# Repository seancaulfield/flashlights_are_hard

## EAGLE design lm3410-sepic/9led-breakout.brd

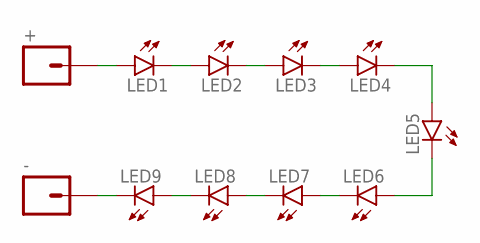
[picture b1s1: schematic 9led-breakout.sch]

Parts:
+: M01PTH-KIT; 1X01-KIT
-: M01NOSILK-KIT; 1X01NS-KIT
LED1, LED2, LED3, LED4, LED5, LED6, LED7, LED8, LED9: LED5MM

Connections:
unnamed: +.1, LED1.A
unnamed: LED1.K (C), LED2.A
unnamed: LED2.K (C), LED3.A
unnamed: LED3.K (C), LED4.A
unnamed: LED4.K (C), LED5.A
unnamed: LED5.K (C), LED6.A
unnamed: LED6.K (C), LED7.A
unnamed: LED7.K (C), LED8.A
unnamed: LED8.K (C), LED9.A
unnamed: -.1, LED9.K (C)

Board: 2 copper layers, 11 parts (0 on the bottom side), 10 nets, no tracks yet.

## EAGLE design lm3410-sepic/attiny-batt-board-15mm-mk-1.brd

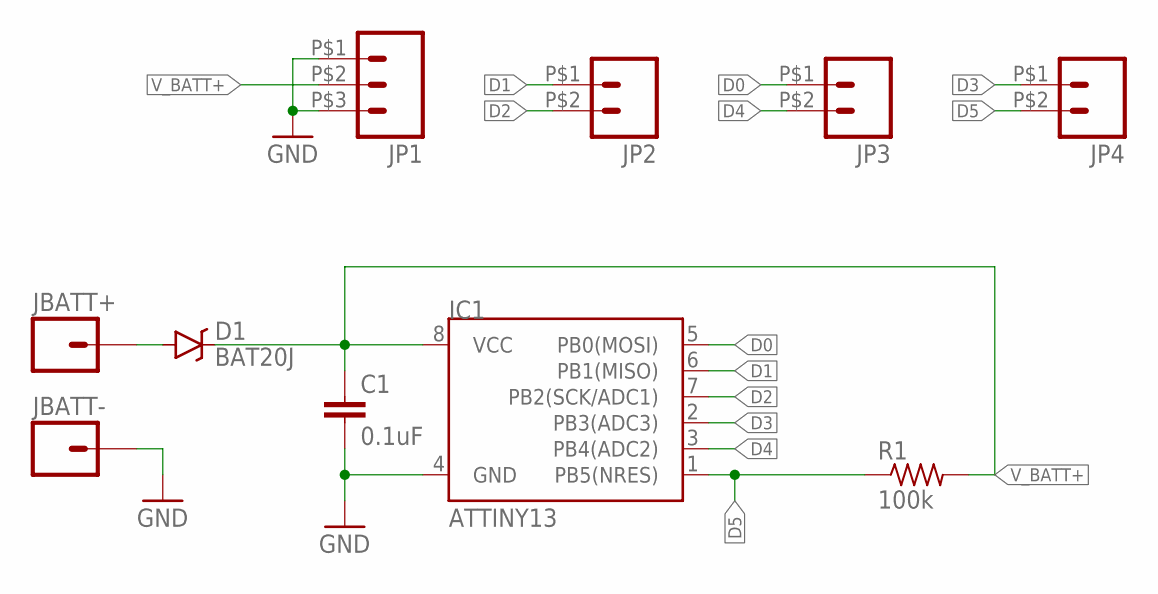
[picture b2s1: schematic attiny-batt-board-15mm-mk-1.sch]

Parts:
C1: 0.1uF; C0603
D1: BAT20J; SOD-323
IC1: ATTINY13; SO08
JBATT+: M01NOT-A-VIA-NOPE; 1X01_NOSILK_NOSTOP
JBATT-: M01NOT-A-VIA-NOPE; 1X01_NOSILK_NOSTOP
JP1: M03PTH-2MM; 1X03-2MM-PTH
JP2, JP3, JP4: M02PTH-2MM; 1X02-2MM-PTH
R1: 100k; R0603

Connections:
BATT_IN: D1.A, JBATT+.P$1
D0: IC1.5 (PB0(MOSI)), JP3.P$1 (1)
D1: IC1.6 (PB1(MISO)), JP2.P$1 (1)
D2: IC1.7 (PB2(SCK/ADC1)), JP2.P$2 (2)
D3: IC1.2 (PB3(ADC3)), JP4.P$1 (1)
D4: IC1.3 (PB4(ADC2)), JP3.P$2 (2)
D5: IC1.1 (PB5(NRES)), JP4.P$2 (2), R1.1
GND: C1.2, IC1.4 (GND), JBATT-.P$1, JP1.P$1 (1), JP1.P$3 (3)
V_BATT+: C1.1, D1.C, IC1.8 (VCC), JP1.P$2 (2), R1.2

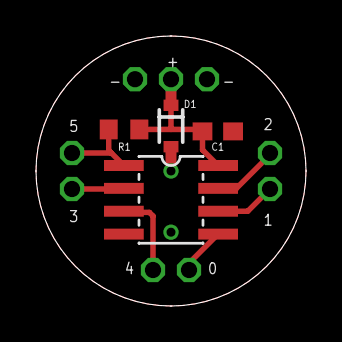
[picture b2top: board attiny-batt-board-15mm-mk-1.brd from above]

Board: 2 copper layers, 15.0 x 15.0 mm, 10 parts (0 on the bottom side), 9 nets.

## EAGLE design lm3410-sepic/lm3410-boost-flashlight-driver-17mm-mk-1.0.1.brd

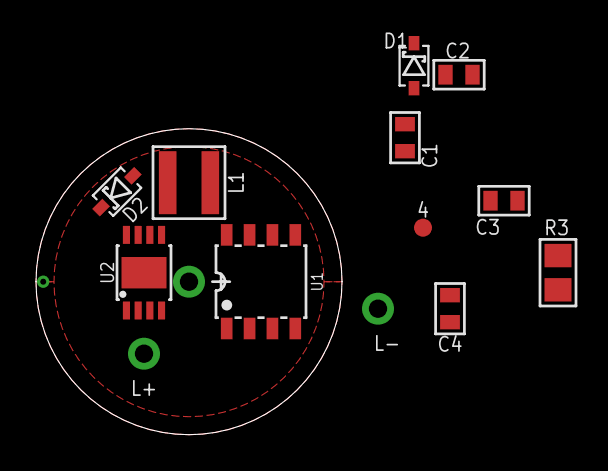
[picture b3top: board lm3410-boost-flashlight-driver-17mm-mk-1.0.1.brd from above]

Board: 2 copper layers, 17.0 x 17.0 mm, 16 parts (1 on the bottom side), 9 nets, no tracks yet.

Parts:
4: M01SMD-1MM-DIA-NS; 1X01-SMD-1MM-DIA-NS
+: M01PTH-1MM-CIR-NS; 1X01-1MM-CIR-NS
-: M01NOT-A-VIA-NOPE; 1X01_NOSILK_NOSTOP
C1, C4: 10u; C0603-TIGHTER
C2: 1u; C0603-TIGHTER
C3: 4u7; C0603-TIGHTER
D1, D2: BAT165; SOD323-SCHOTTKY
FRAME1: FRAME-LETTERNO_PACKAGE; DUMMY
L1: 1uH; XFL4020
L+: M01PTH-1MM-CIR-NS; 1X01-1MM-CIR-NS
L-: M01PTH-1MM-CIR-NS; 1X01-1MM-CIR-NS
R3: 0R127; R0805
U1: Tiny25; SO08-SKINNYPADS
U2: LM3410XMYDGN; MSOP-8-PAD-LM3410

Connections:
4: 4.P$1, U1.3
FB: L-.1, R3.2, U2.5
GND: -.P$1, C1.2, C2.2, C3.2, C4.2, R3.1, U1.4, U2.2, U2.6, U2.PAD
LED+: C4.1, D2.C, L+.1
unnamed: C2.1, U1.2
PWM: U1.6, U2.4
SW: D2.A, L1.P$2, U2.7
VBAT: +.1, C3.1, D1.A, L1.P$1, U2.3
VCC: C1.1, D1.C, U1.1, U1.8

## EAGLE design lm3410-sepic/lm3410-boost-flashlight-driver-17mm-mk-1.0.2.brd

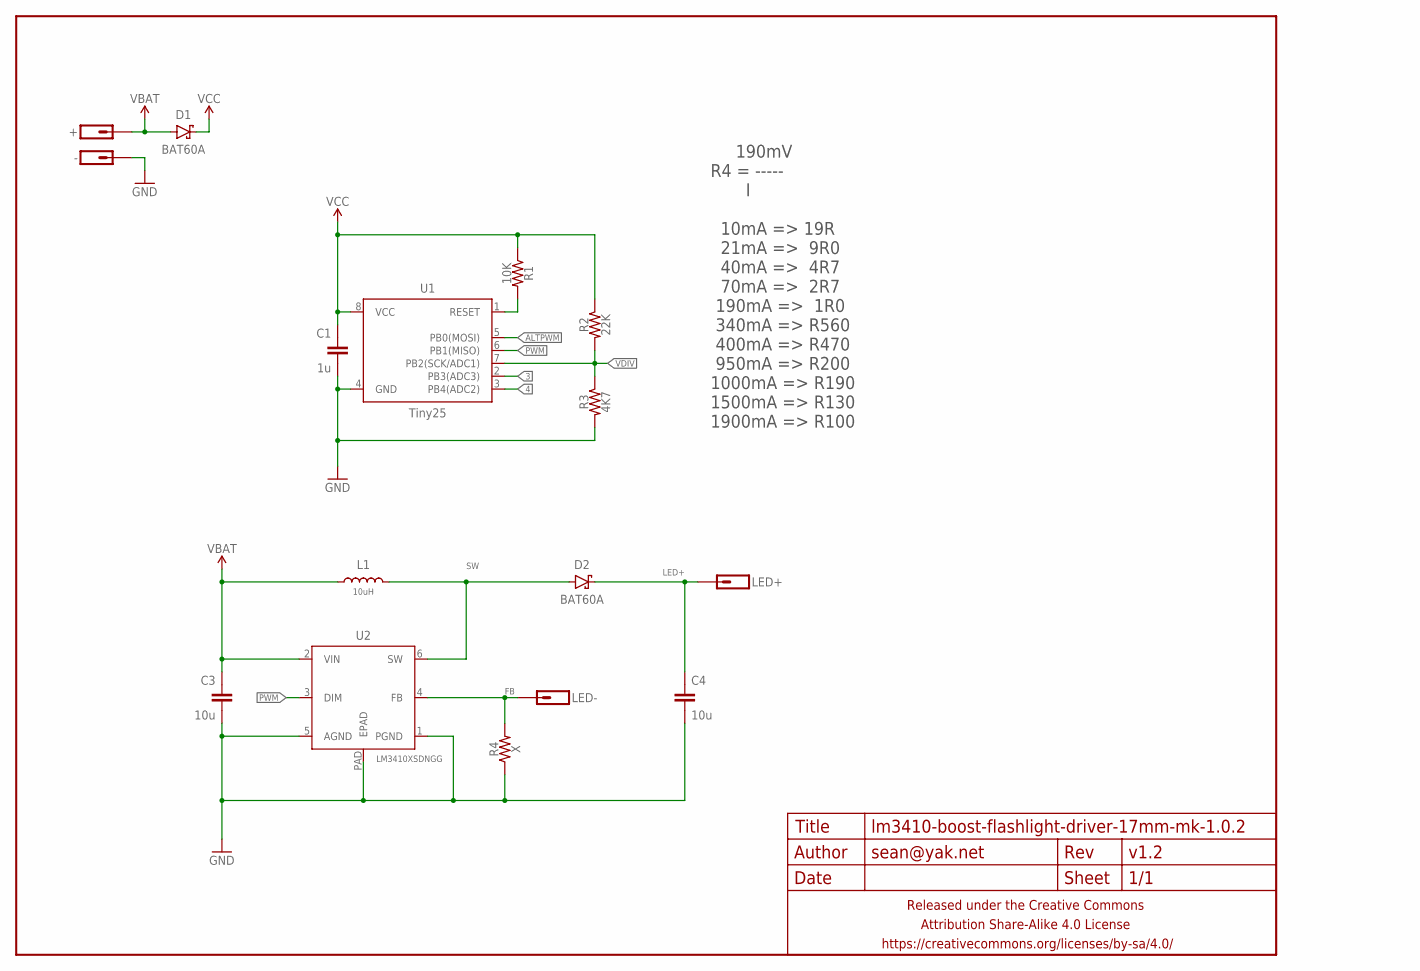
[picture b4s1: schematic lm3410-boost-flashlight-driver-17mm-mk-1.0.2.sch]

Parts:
+: M01PTH-1MM-CIR-NS; 1X01-1MM-CIR-NS
-: M01NOT-A-VIA-NOPE; 1X01_NOSILK_NOSTOP
C1: 1u; C0402
C3, C4: 10u; C0805-TIGHTER
D1, D2: BAT60A; SOD323-SCHOTTKY
FRAME1: FRAME-LETTERNO_PACKAGE; DUMMY
L1: 10uH; XFL4020
LED+: M01PTH-1MM-CIR-NS; 1X01-1MM-CIR-NS
LED-: M01PTH-1MM-CIR-NS; 1X01-1MM-CIR-NS
R1: 10K; R0402
R2: 22K; R0402
R3: 4K7; R0402
R4: X; R0805-TIGHTER
U1: Tiny25; SO08-SKINNYPADS
U2: LM3410XSDNGG; DFN300X300X80-7N

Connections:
3: U1.2 (PB3(ADC3))
4: U1.3 (PB4(ADC2))
ALTPWM: U1.5 (PB0(MOSI))
FB: LED-.1, R4.2, U2.4 (FB)
GND: -.P$1, C1.2, C3.2, C4.2, R3.2, R4.1, U1.4 (GND), U2.1 (PGND), U2.5 (AGND), U2.PAD (EPAD)
LED+: C4.1, D2.C, LED+.1
unnamed: R1.2, U1.1 (RESET)
PWM: U1.6 (PB1(MISO)), U2.3 (DIM)
SW: D2.A, L1.P$2 (2), U2.6 (SW)
VBAT: +.1, C3.1, D1.A, L1.P$1 (1), U2.2 (VIN)
VCC: C1.1, D1.C, R1.1, R2.1, U1.8 (VCC)
VDIV: R2.2, R3.1, U1.7 (PB2(SCK/ADC1))

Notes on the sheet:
190mV R4 = ----- I 10mA => 19R 21mA => 9R0 40mA => 4R7 70mA => 2R7 190mA => 1R0 340mA => R560 400mA => R470 950mA => R200 1000mA => R190 1500mA => R130 1900mA => R100

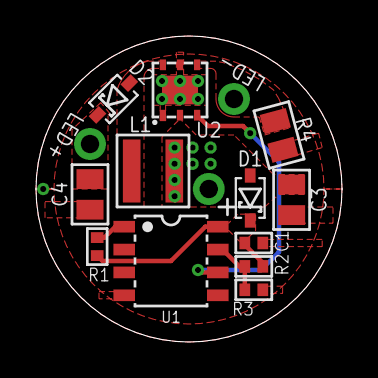
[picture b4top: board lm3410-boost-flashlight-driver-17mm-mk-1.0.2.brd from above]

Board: 2 copper layers, 17.0 x 17.0 mm, 17 parts (1 on the bottom side), 9 nets.

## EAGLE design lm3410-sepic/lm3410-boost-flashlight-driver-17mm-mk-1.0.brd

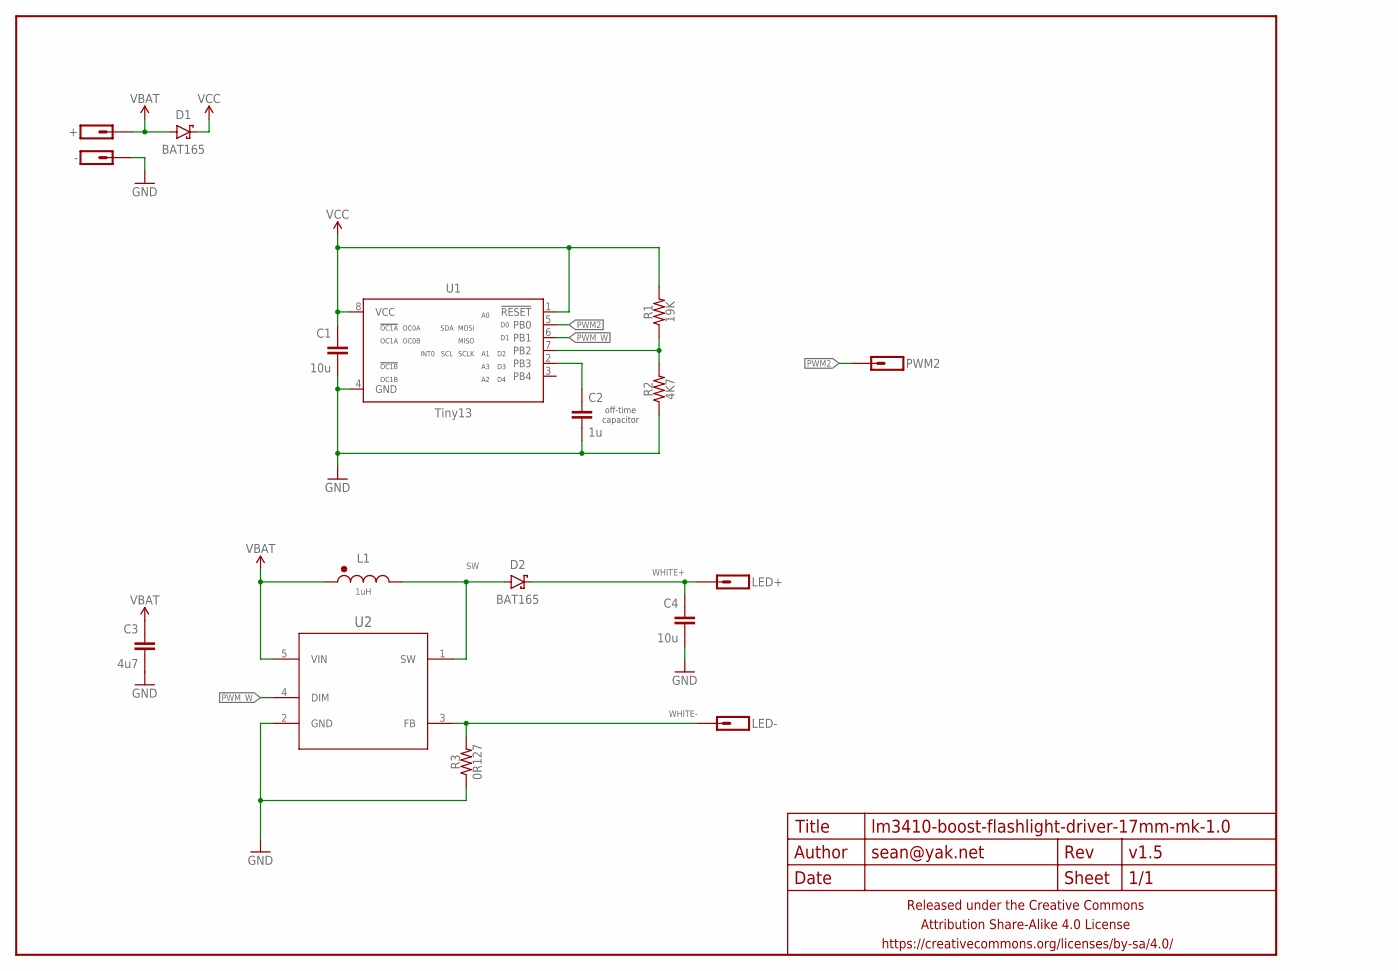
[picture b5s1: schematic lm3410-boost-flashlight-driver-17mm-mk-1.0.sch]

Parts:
+: M01PTH-1MM-CIR-NS; 1X01-1MM-CIR-NS
-: M01NOT-A-VIA-NOPE; 1X01_NOSILK_NOSTOP
C1, C4: 10u; C0603-TIGHTER
C2: 1u; C0603-TIGHTER
C3: 4u7; C0603-TIGHTER
D1, D2: BAT165; SOD323-SCHOTTKY
FRAME1: FRAME-LETTERNO_PACKAGE; DUMMY
L1: 1uH; LPS4012
LED+: M01PTH-1.2MM-NS; 1X01-1.2MM-NS
LED-: M01PTH-1.2MM-NS; 1X01-1.2MM-NS
PWM2: M01SMD-1MM-DIA-NS; 1X01-SMD-1MM-DIA-NS
R1: 19K; R0603-TIGHTER
R2: 4K7; R0603-TIGHTER
R3: 0R127; R0805
U1: Tiny13; SO08-NARROWER
U2: LM3410XMF; SOT95P285X120-5N

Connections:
GND: -.P$1, C1.2, C2.2, C3.2, C4.2, R2.1, R3.1, U1.4 (GND), U2.2 (GND)
unnamed: R1.1, R2.2, U1.7 (PB2)
unnamed: C2.1, U1.2 (PB3)
PWM2: PWM2.P$1, U1.5 (PB0)
PWM_W: U1.6 (PB1), U2.4 (DIM)
SW: D2.A, L1.P$2 (2), U2.1 (SW)
VBAT: +.1, C3.1, D1.A, L1.P$1 (1), U2.5 (VIN)
VCC: C1.1, D1.C, R1.2, U1.1 (!RESET), U1.8 (VCC)
WHITE+: C4.1, D2.C, LED+.P$1
WHITE-: LED-.P$1, R3.2, U2.3 (FB)

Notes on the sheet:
off-time capacitor

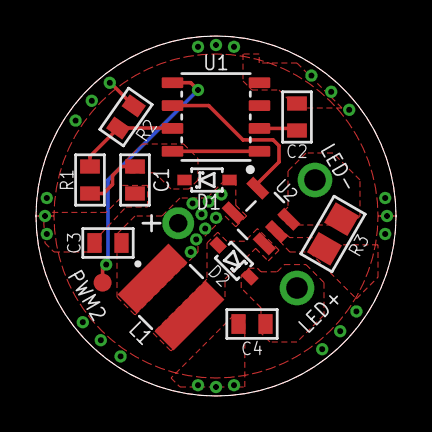
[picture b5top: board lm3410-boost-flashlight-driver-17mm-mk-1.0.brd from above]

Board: 2 copper layers, 20.0 x 20.0 mm, 18 parts (1 on the bottom side), 10 nets.

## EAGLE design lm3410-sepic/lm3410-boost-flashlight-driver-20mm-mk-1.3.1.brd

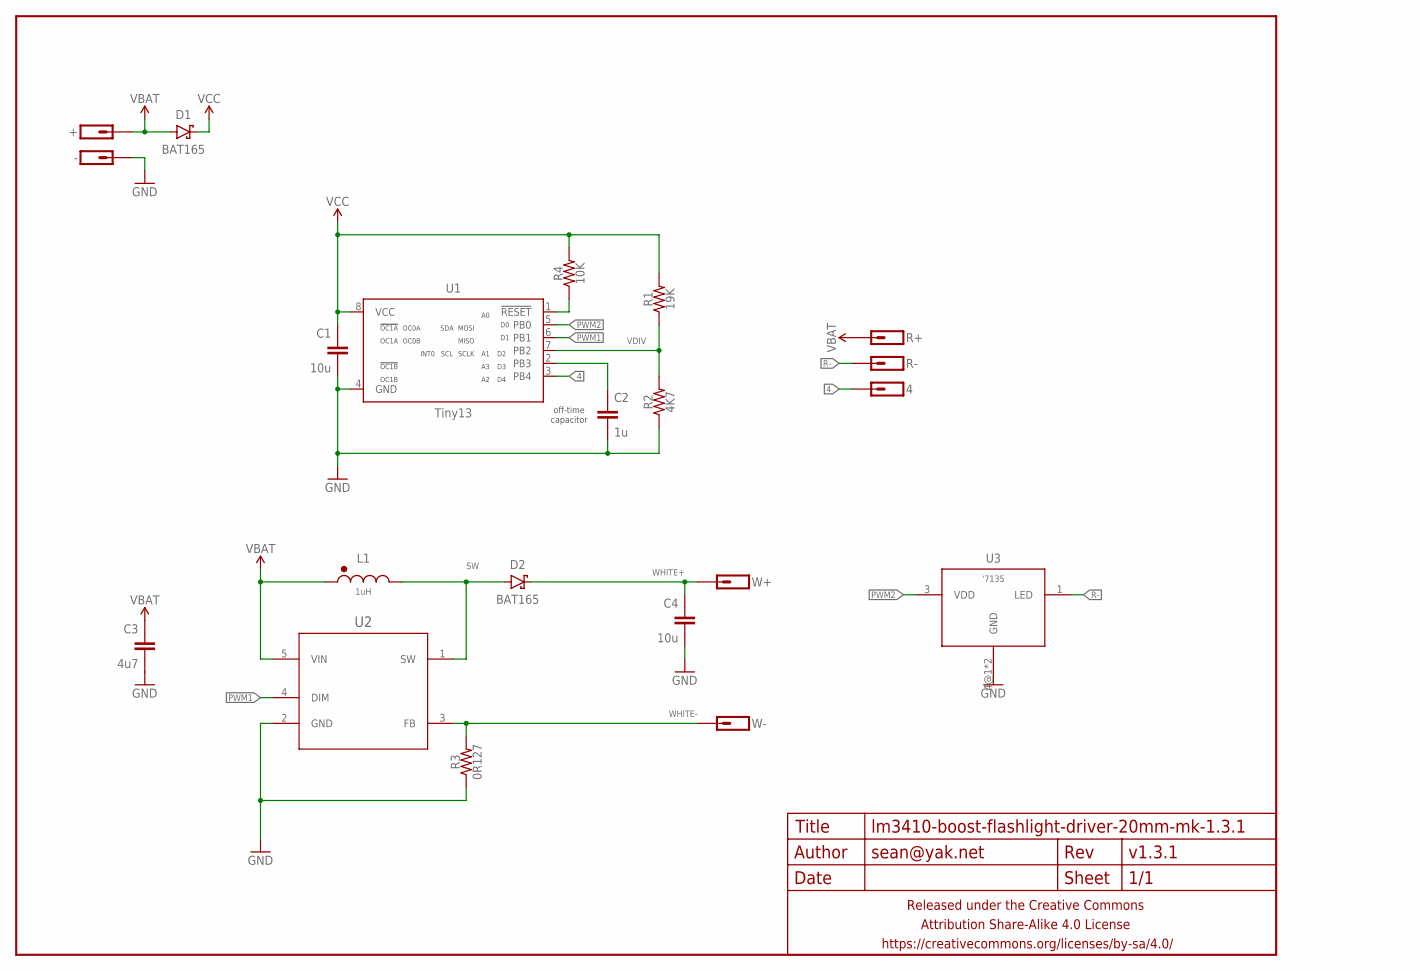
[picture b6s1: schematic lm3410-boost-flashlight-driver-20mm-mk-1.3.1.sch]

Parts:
4: M01SMD-1MM-DIA-NS; 1X01-SMD-1MM-DIA-NS
+: M01PTH-1MM-CIR-NS; 1X01-1MM-CIR-NS
-: M01NOT-A-VIA-NOPE; 1X01_NOSILK_NOSTOP
C1, C4: 10u; C0603-TIGHTER
C2: 1u; C0603-TIGHTER
C3: 4u7; C0603-TIGHTER
D1: BAT165; SOD323-SCHOTTKY
D2: BAT165; SOD123-SCHOTTKY
FRAME1: FRAME-LETTERNO_PACKAGE; DUMMY
L1: 1uH; PFL2512
R1: 19K; R0603-TIGHTER
R2: 4K7; R0603-TIGHTER
R3: 0R127; R0805
R4: 10K; R0402
R+: M01SMD-1MM-DIA-NS; 1X01-SMD-1MM-DIA-NS
R-: M01SMD-1MM-DIA-NS; 1X01-SMD-1MM-DIA-NS
U1: Tiny13; SO08-NARROWER
U2: LM3410XMF; SOT95P285X120-5N
U3: '7135; SOT89-NOTHERM
W+: M01PTH-1.2MM-NS; 1X01-1.2MM-NS
W-: M01PTH-1.2MM-NS; 1X01-1.2MM-NS

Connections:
4: 4.P$1, U1.3 (PB4)
GND: -.P$1, C1.2, C2.2, C3.2, C4.2, R2.1, R3.1, U1.4 (GND), U2.2 (GND), U3.4@1 (GND), U3.4@2 (GND)
unnamed: R4.1, U1.1 (!RESET)
unnamed: C2.1, U1.2 (PB3)
PWM1: U1.6 (PB1), U2.4 (DIM)
PWM2: U1.5 (PB0), U3.3 (VDD)
R-: R-.P$1, U3.1 (LED)
SW: D2.A, L1.P$2 (2), U2.1 (SW)
VBAT: +.1, C3.1, D1.A, L1.P$1 (1), R+.P$1, U2.5 (VIN)
VCC: C1.1, D1.C, R1.2, R4.2, U1.8 (VCC)
VDIV: R1.1, R2.2, U1.7 (PB2)
WHITE+: C4.1, D2.C, W+.P$1
WHITE-: R3.2, U2.3 (FB), W-.P$1

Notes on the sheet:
off-time capacitor

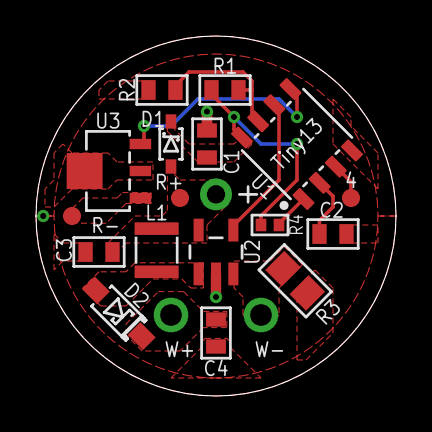
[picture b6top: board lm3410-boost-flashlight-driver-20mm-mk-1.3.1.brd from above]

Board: 2 copper layers, 20.0 x 20.0 mm, 22 parts (1 on the bottom side), 13 nets.

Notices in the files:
parts and their libraries:
SparkFun-Aesthetics: Licensing: Creative Commons ShareAlike 4.0 International - https://creativecommons.org/licenses/by-sa/4.0
a_parts: Released under the Creative Commons Attribution Share-Alike 4.0 License
a_parts: https://creativecommons.org/licenses/by-sa/4.0
